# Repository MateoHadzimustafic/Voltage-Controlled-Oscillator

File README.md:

# Voltage-Controlled-Oscillator

## Overview

Designed and built a Voltage-Controlled Oscillator (VCO) capable of generating square and triangle waveforms with adjustable frequency and amplitude using op-amp-based analog circuitry. Integrated USB power management and LiPo battery input for portable or wired operation, including onboard LiPo charging functionality for convenient rechargeable power support.

## Current Status

Completed — Fully designed, built, tested, and validated.

## Features

- Square Wave Generator
- Triangle Wave Generator
- Frequency Control
- Amplitude Control
- Lipo Battery and USB-C Powered
- Lipo Battery Charger

## Repository Structure

- `docs/` — design notes, calculations, and planning
- `hardware/` — schematic, PCB layout, and manufacturing files
- `bom/` — bill of materials and component notes
- `images/` — renders, diagrams, and photos

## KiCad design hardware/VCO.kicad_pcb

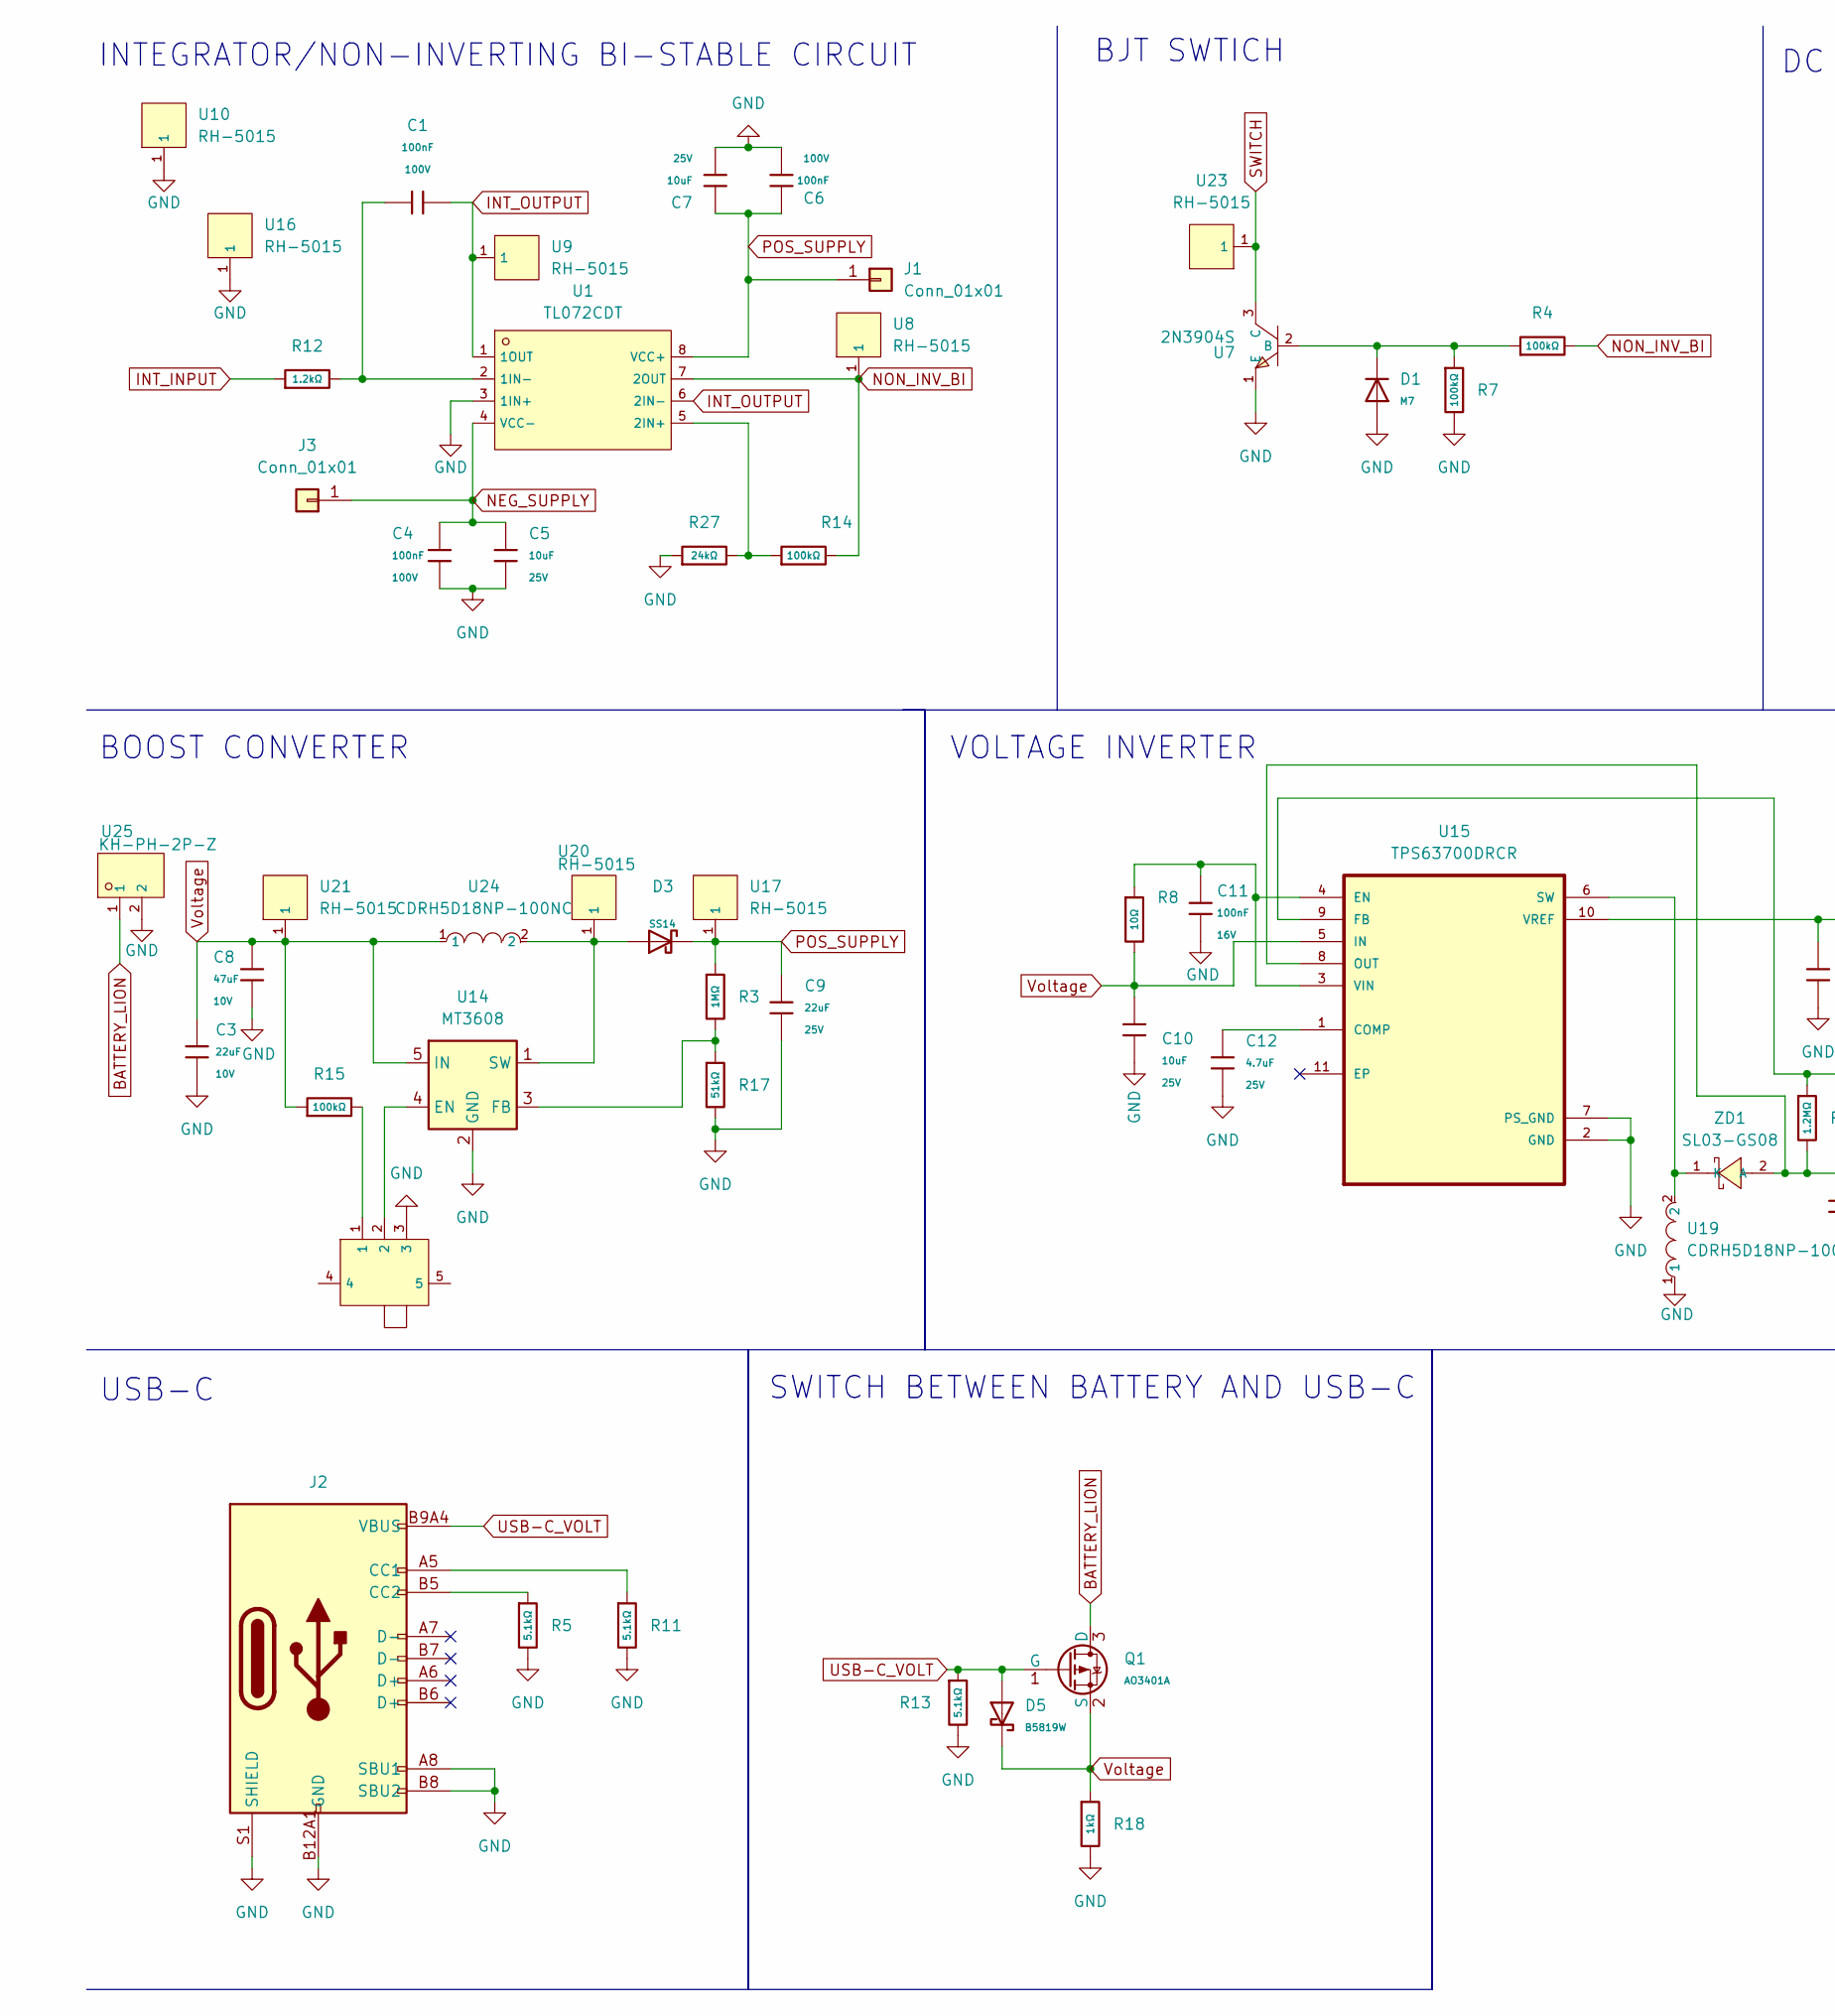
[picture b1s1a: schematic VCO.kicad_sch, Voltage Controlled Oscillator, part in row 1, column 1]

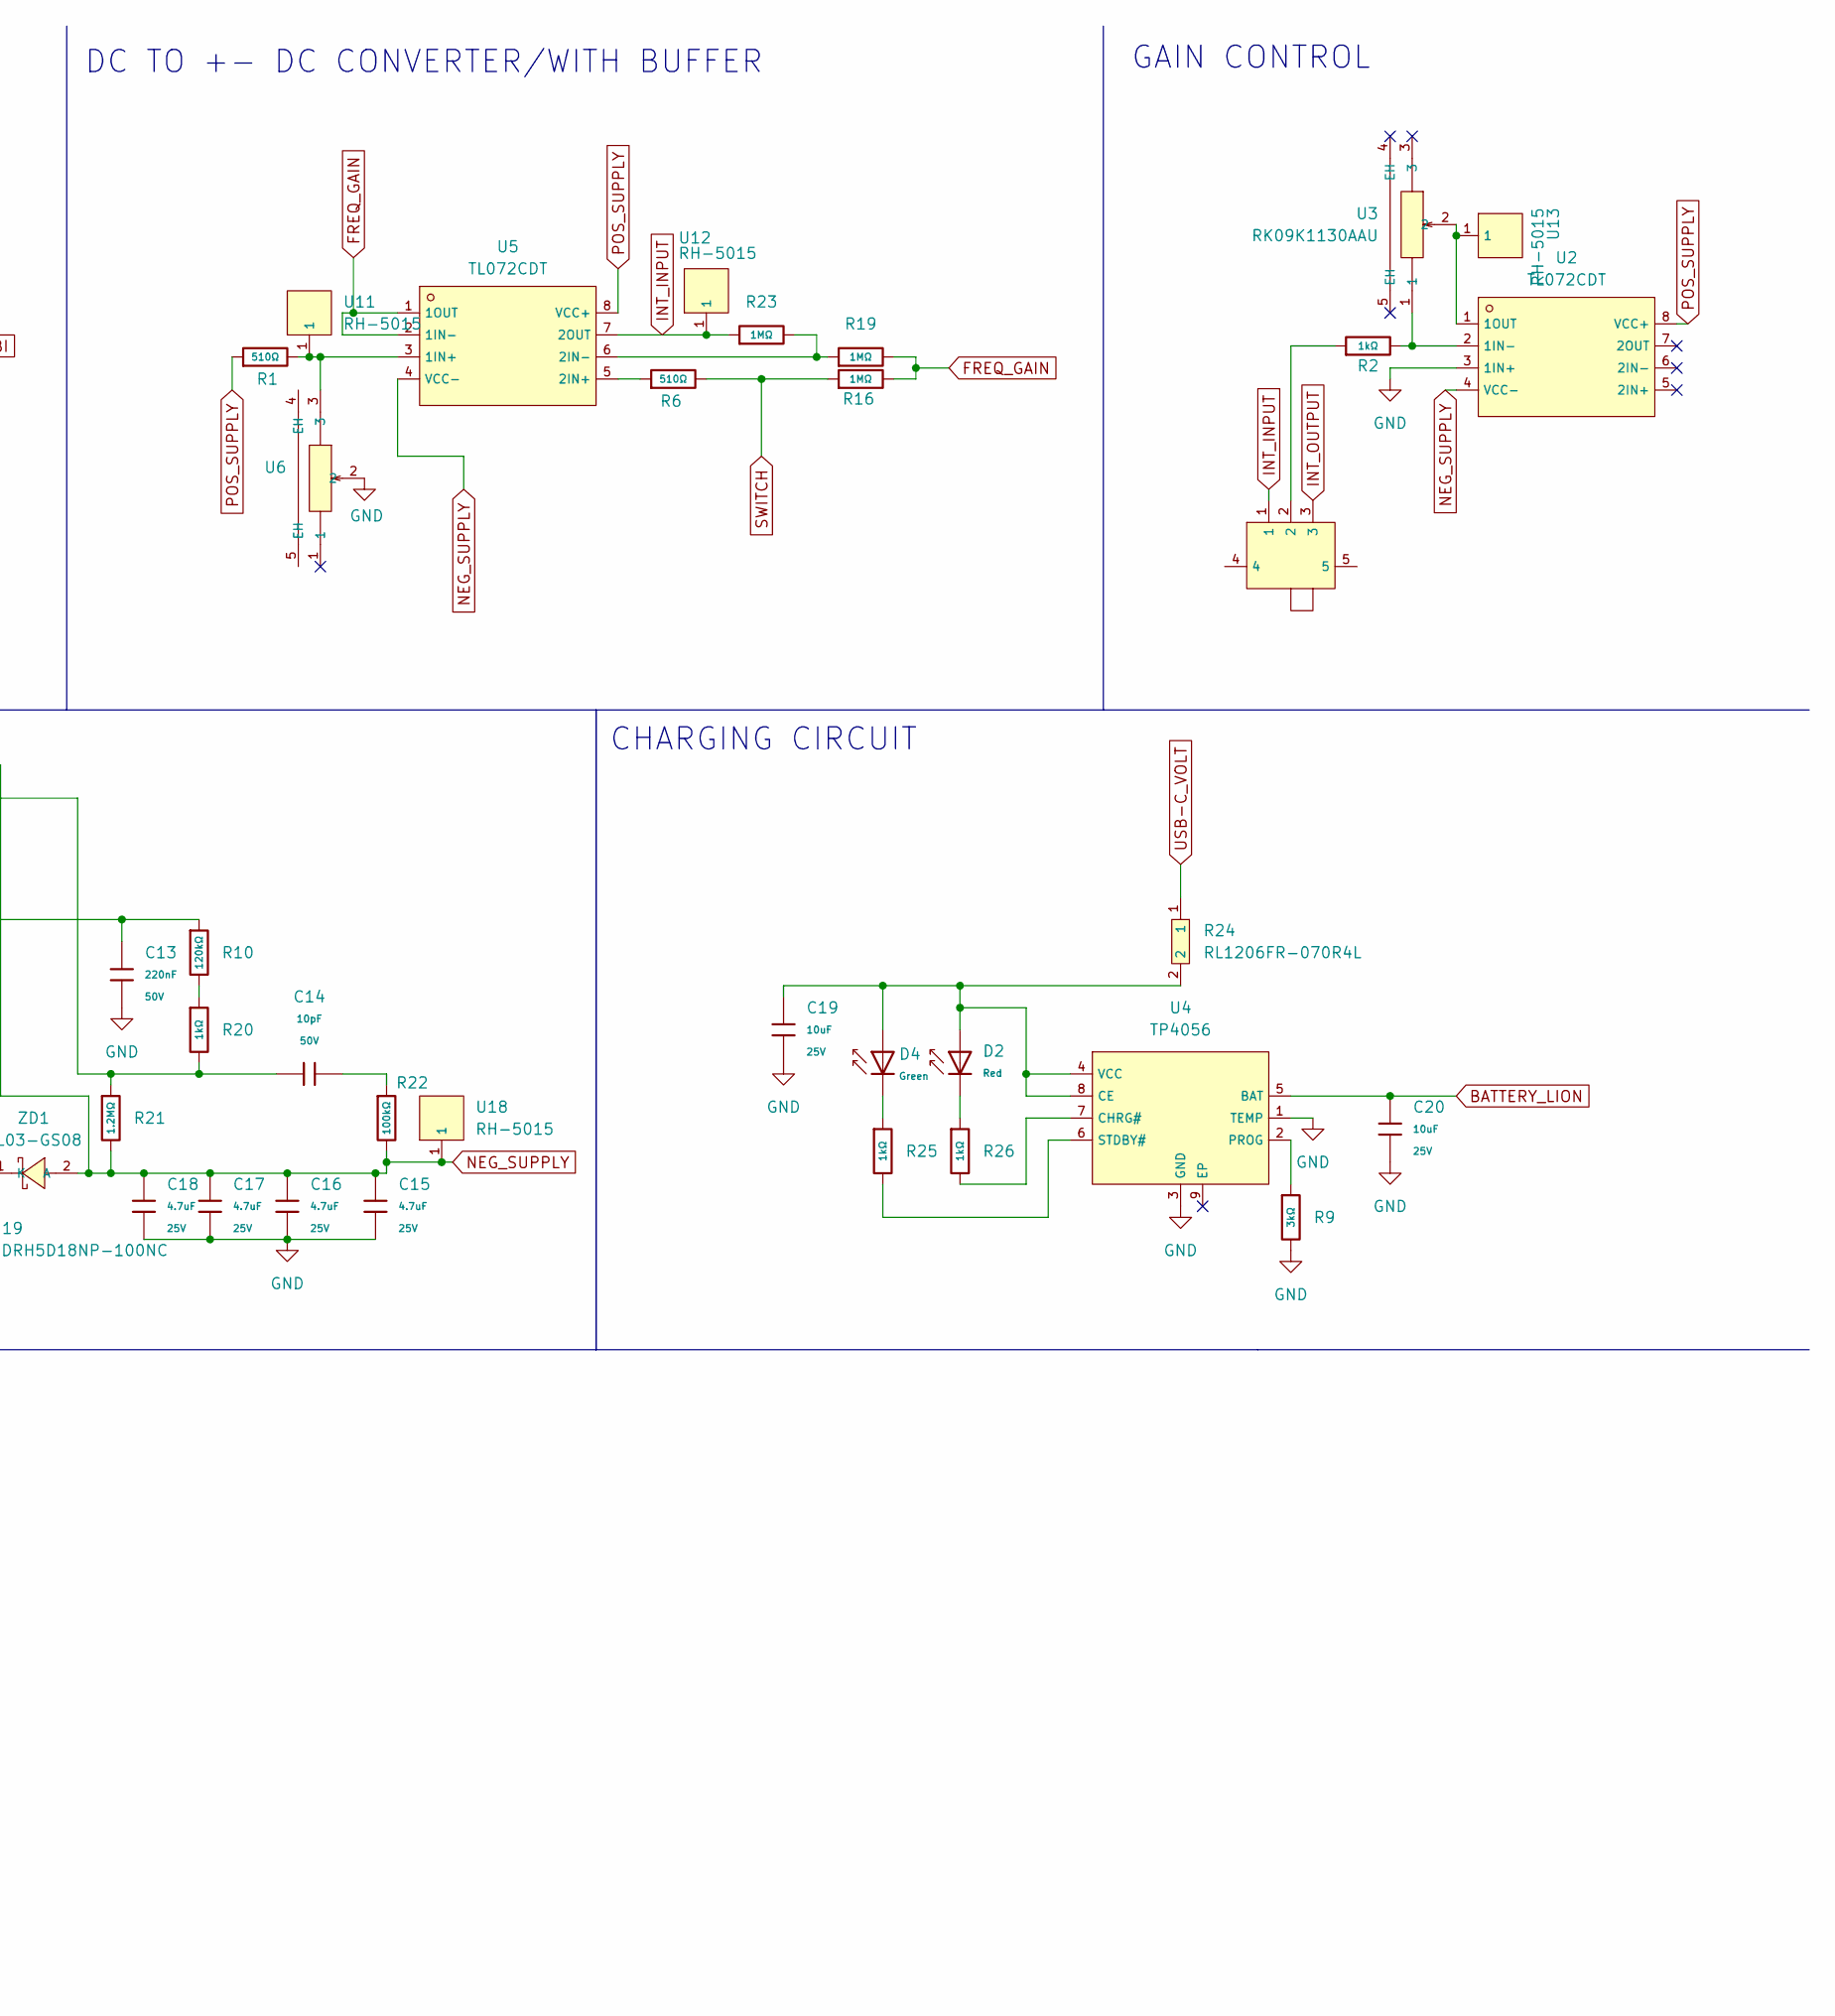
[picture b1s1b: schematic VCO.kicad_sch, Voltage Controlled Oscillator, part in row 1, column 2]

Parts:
C1, C4, C6: 100nF; C_0805; Voltage Rated 100V; Tolerance ±10%; Part CL21B104KCFNNNE; LCSC C28233
C3: 22uF; C_1206; Voltage Rated 10V; Tolerance ±10%; Part CL31A226KPHNNNE; LCSC C5672
C5, C7, C10, C19, C20: 10uF; C_0805; Voltage Rated 25V; Tolerance ±10%; Part CL21A106KAYNNNE; LCSC C15850
C8: 47uF; C_1206; Voltage Rated 10V; Tolerance ±20%; Part CL31A476MPHNNNE; LCSC C96123
C9: 22uF; C_0805; Voltage Rated 25V; Tolerance ±20%; Part CL21A226MAQNNNE; LCSC C45783
C11: 100nF; C_0402; Voltage Rated 16V; Tolerance ±10%; Part CL05B104KO5NNNC; LCSC C1525
C12, C15, C16, C17, C18: 4.7uF; C_0805; Voltage Rated 25V; Tolerance ±10%; Part CL21A475KAQNNNE; LCSC C1779
C13: 220nF; C_0805; Voltage Rated 50V; Tolerance ±10%; Part CL21B224KBFNNNE; LCSC C5378
C14: 10pF; C_0603; Voltage Rated 50V; Tolerance ±5%; Part CL10C100JB8NNNC; LCSC C1634
D1: M7; D_SMA; Forward Voltage (Vf@If) 1.1V@1A; Reverse Voltage (Vr) 1kV; Part M7; LCSC C95872
D2: Red; D_0805; Forward Voltage (VF) 1.6V~2.6V; Part NCD0805R1; LCSC C84256
D3: SS14; D_SMA; Forward Voltage (Vf@If) 0.55V@1.0A; Reverse Voltage (Vr) 40V; Part SS14; LCSC C7420316
D4: Green; D_0805; Part KT-0805G; LCSC C2297
D5: B5819W; D_SOD-123; Forward Voltage (Vf@If) 900mV@3A; Reverse Voltage (Vr) 40V; Part B5819W; LCSC C64885
J1, J3: Conn_01x01; PinHeader_1x01_P1.00mm_Vertical
J2: Connector, USB-TYPE-C-16P; TYPE-C-SMD_HX-TYPE-C-16PIN; LCSC C2927039
Q1: AO3401A; Q_SOT-23; Part AO3401A; LCSC C15127
R1, R6: 510Ω; R_0805; Overload Voltage (Max) 150V; Tolerance ±1%; Part 0805W8F5100T5E; LCSC C17734
R2, R18, R20, R25, R26: 1kΩ; R_0805; Overload Voltage (Max) 150V; Tolerance ±1%; Part 0805W8F1001T5E; LCSC C17513
R3, R16, R19, R23: 1MΩ; R_0805; Overload Voltage (Max) 150V; Tolerance ±1%; Part 0805W8F1004T5E; LCSC C17514
R4, R7, R14, R15, R22: 100kΩ; R_0805; Overload Voltage (Max) 150V; Tolerance ±1%; Part 0805W8F1003T5E; LCSC C149504
R5, R11, R13: 5.1kΩ; R_0805; Overload Voltage (Max) 150V; Tolerance ±1%; Part 0805W8F5101T5E; LCSC C27834
R8: 10Ω; R_0603; Overload Voltage (Max) 75V; Tolerance ±1%; Part 0603WAF100JT5E; LCSC C22859
R9: 3kΩ; R_0805; Overload Voltage (Max) 150V; Tolerance ±1%; Part 0805W8F3001T5E; LCSC C17661
R10: 120kΩ; R_0805; Overload Voltage (Max) 150V; Tolerance ±1%; Part 0805W8F1203T5E; LCSC C17436
R12: 1.2kΩ; R_0805; Overload Voltage (Max) 150V; Tolerance ±1%; Part 0805W8F1201T5E; LCSC C17379
R17: 51kΩ; R_0805; Overload Voltage (Max) 150V; Tolerance ±1%; Part 0805W8F5102T5E; LCSC C17737
R21: 1.2MΩ; R_1206; Overload Voltage (Max) 200V; Tolerance ±1%; Part 1206W4F1204T5E; LCSC C22107
R24: RL1206FR-070R4L; R1206; LCSC C327078
R27: 24kΩ; R_0805; Overload Voltage (Max) 150V; Tolerance ±1%; Part 0805W8F2402T5E; LCSC C17575
SW1, SW2: SS12D07VG6_087; SW-TH_SS12D07VG4; LCSC C2939728
U1, U2, U5: TL072CDT; SOIC-8_L5.0-W4.0-P1.27-LS6.0-BL; Voltage - Input Offset(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 3mV; Part TL072CDT; LCSC C6961
U3, U6: RK09K1130AAU; RES-TH_RK09K1130AAU; LCSC C202373
U4: TP4056; ESOP-8_L4.9-W3.9-P1.27-LS6.0-BL-EP; Part TP4056-42-ESOP8; LCSC C16581
U7: 2N3904S; SOT-23-3_L2.9-W1.3-P1.90-LS2.4-TR; LCSC C18536
U8, U9, U10, U11, U12, U13, U16, U17, U18, U20, U21, U23: RH-5015; SMD_RH-5015; LCSC C5199798
U14: MT3608; SOT-23-6_L2.9-W1.6-P0.95-LS2.8-BL; LCSC C84817
U15: TPS63700DRCR; VREG_V62_16624-01YE; LCSC C54792
U19, U24: CDRH5D18NP-100NC; IND-SMD_L5.7-W5.7_CDRH5D18NP; LCSC C113636
U25: KH-PH-2P-Z; CONN-TH_2P-P2.00_KINGHELM_KH-PH-2P-Z; LCSC C2898945
ZD1: SL03-GS08; SMF_L2.8-W1.8-LS3.7-RD; LCSC C490381

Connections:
BATTERY_LION: C20.1, Q1.3 (D), U4.5 (BAT), U25.1
FREQ_GAIN: R16.2, R19.2, U5.1 (1OUT), U5.2 (1IN-)
GND: C3.2, C4.2, C5.2, C6.2, C7.2, C8.2, C9.2, C10.2, C11.2, C12.2, C13.2, C15.2, C16.2, C17.2, C18.2, C19.2, C20.2, D1.2, J2.A8 (SBU1), J2.A12B1 (GND), J2.B8 (SBU2), J2.B12A1 (GND), J2.S1 (SHIELD), R5.2, R7.2, R9.2, R11.2, R13.2, R17.2, R18.2, R27.1, SW1.3, U1.3 (1IN+), U2.3 (1IN+), U4.1 (TEMP), U4.3 (GND), U6.2, U7.1 (E), U10.1, U14.2 (GND), U15.2 (GND), U15.7 (PS_GND), U16.1, U19.1, U25.2
INT_INPUT: R12.1, R23.1, SW2.1, U5.7 (2OUT), U12.1
INT_OUTPUT: C1.2, SW2.3, U1.1 (1OUT), U1.6 (2IN-), U9.1
NEG_SUPPLY: C4.1, C5.1, C15.1, C16.1, C17.1, C18.1, J3.1, R21.2, R22.2, U1.4 (VCC-), U2.4 (VCC-), U5.4 (VCC-), U15.8 (OUT), U18.1, ZD1.2 (A)
NON_INV_BI: R4.2, R14.2, U1.7 (2OUT), U8.1
unnamed: C14.2, R22.1
unnamed: D2.1, R26.1
unnamed: D4.1, R25.1
unnamed: J2.A5 (CC1), R11.1
unnamed: J2.B5 (CC2), R5.1
unnamed: R2.1, SW2.2
unnamed: R10.2, R20.1
unnamed: R15.2, SW1.1
unnamed: C1.1, R12.2, U1.2 (1IN-)
unnamed: R14.1, R27.2, U1.5 (2IN+)
unnamed: R2.2, U2.2 (1IN-), U3.1
unnamed: U2.1 (1OUT), U3.2, U13.1
unnamed: C19.1, D2.2, D4.2, R24.2, U4.4 (VCC), U4.8 (CE)
unnamed: R26.2, U4.7 (CHRG#)
unnamed: R9.1, U4.2 (PROG)
unnamed: R25.2, U4.6 (STDBY#)
unnamed: R1.2, U5.3 (1IN+), U6.3, U11.1
unnamed: R6.1, U5.5 (2IN+)
unnamed: R19.1, R23.2, U5.6 (2IN-)
unnamed: D1.1, R4.1, R7.1, U7.2 (B)
unnamed: SW1.2, U14.4 (EN)
unnamed: R3.2, R17.1, U14.3 (FB)
unnamed: D3.2, U14.1 (SW), U20.1, U24.2
unnamed: C12.1, U15.1 (COMP)
unnamed: C11.1, R8.1, U15.3 (VIN), U15.4 (EN)
unnamed: C14.1, R20.2, R21.1, U15.9 (FB)
unnamed: U15.6 (SW), U19.2, ZD1.1 (K)
unnamed: C13.1, R10.1, U15.10 (VREF)
POS_SUPPLY: C6.1, C7.1, C9.1, D3.1, J1.1, R1.1, R3.1, U1.8 (VCC+), U2.8 (VCC+), U5.8 (VCC+), U17.1
SWITCH: R6.2, R16.1, U7.3 (C), U23.1
USB-C_VOLT: D5.2, J2.A9B4 (VBUS), J2.B9A4 (VBUS), Q1.1 (G), R13.1, R24.1
Voltage: C3.1, C8.1, C10.1, D5.1, Q1.2 (S), R8.2, R15.1, R18.1, U14.5 (IN), U15.5 (IN), U21.1, U24.1

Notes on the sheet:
BJT SWTICH
GAIN CONTROL
VOLTAGE INVERTER
DC TO +- DC CONVERTER/WITH BUFFER
CHARGING CIRCUIT
SWITCH BETWEEN BATTERY AND USB-C
USB-C
INTEGRATOR/NON-INVERTING BI-STABLE CIRCUIT
BOOST CONVERTER

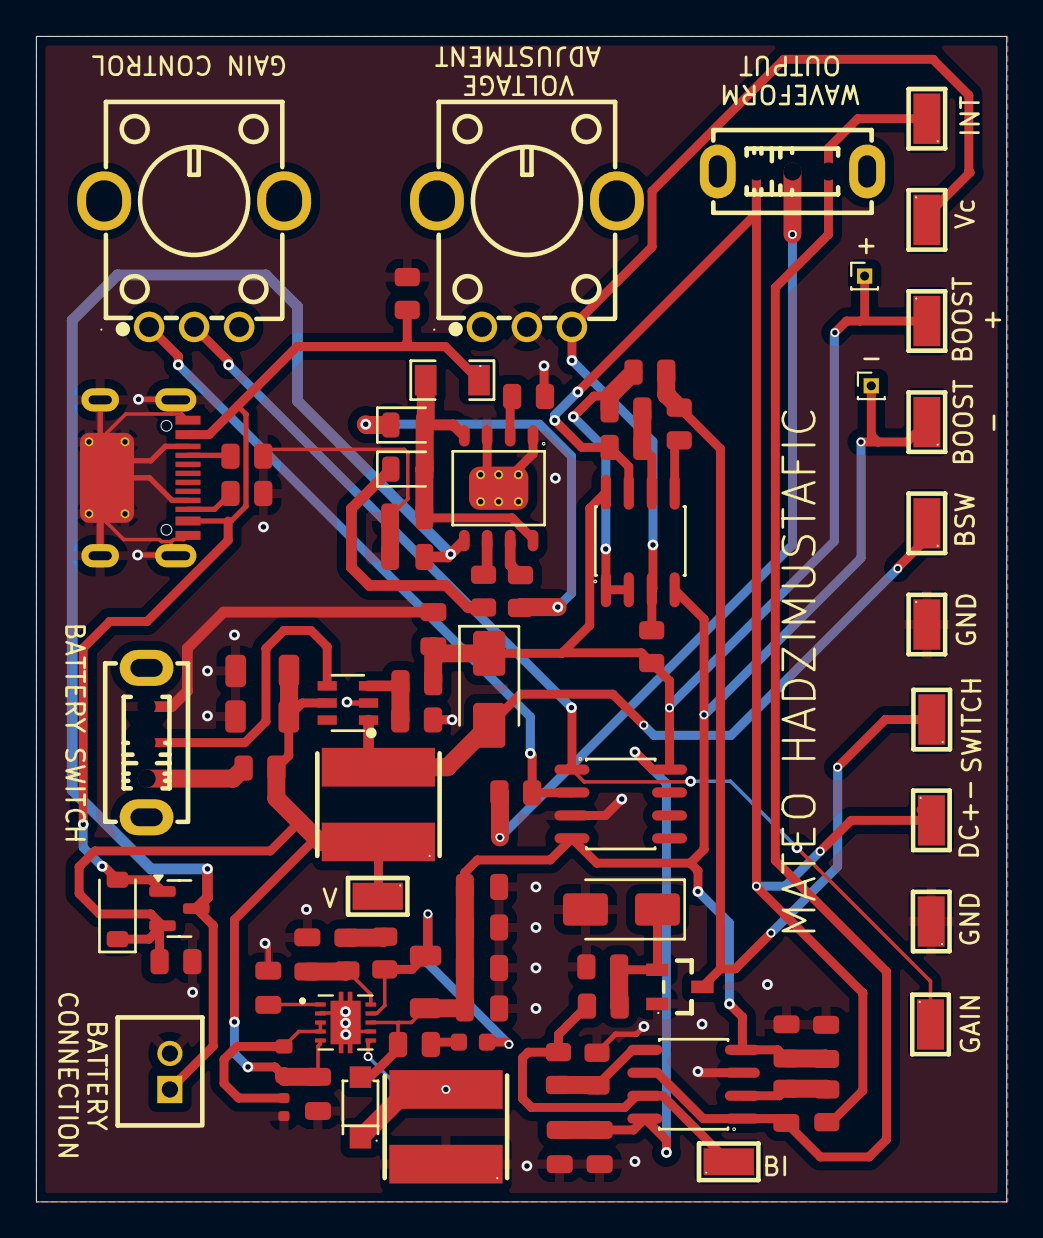
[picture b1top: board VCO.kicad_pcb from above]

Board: 2 copper layers, 53.9 x 64.8 mm, 82 parts (0 on the bottom side), 39 nets.

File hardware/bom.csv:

Designator,Footprint,Quantity,Value,LCSC Part #
"C1, C4, C6",C_0805,3,100nF,C28233
"C10, C19, C20, C5, C7",C_0805,5,10uF,C15850
C11,C_0402,1,100nF,C1525
"C12, C15, C16, C17, C18",C_0805,5,4.7uF,C1779
C13,C_0805,1,220nF,C5378
C14,C_0603,1,10pF,C1634
C3,C_1206,1,22uF,C5672
C8,C_1206,1,47uF,C96123
C9,C_0805,1,22uF,C45783
D1,D_SMA,1,M7,C95872
D2,D_0805,1,Red,C84256
D3,D_SMA,1,SS14,C7420316
D4,D_0805,1,Green,C2297
D5,D_SOD-123,1,B5819W,C64885
"J1, J3",PinHeader_1x01_P1.00mm_Vertical,2,Conn_01x01,
J2,TYPE-C-SMD_HX-TYPE-C-16PIN,1,"Connector, USB-TYPE-C-16P",C2927039
Q1,Q_SOT-23,1,AO3401A,C15127
"R1, R6",R_0805,2,510Ω,C17734
R10,R_0805,1,120kΩ,C17436
"R11, R13, R5",R_0805,3,5.1kΩ,C27834
R12,R_0805,1,1.2kΩ,C17379
"R14, R15, R22, R4, R7",R_0805,5,100kΩ,C149504
"R16, R19, R23, R3",R_0805,4,1MΩ,C17514
R17,R_0805,1,51kΩ,C17737
"R18, R2, R20, R25, R26",R_0805,5,1kΩ,C17513
R21,R_1206,1,1.2MΩ,C22107
R24,R1206,1,RL1206FR-070R4L,C327078
R27,R_0805,1,24kΩ,C17575
R8,R_0603,1,10Ω,C22859
R9,R_0805,1,3kΩ,C17661
"SW1, SW2",SW-TH_SS12D07VG4,2,SS12D07VG6_087,C2939728
"U1, U2, U5",SOIC-8_L5.0-W4.0-P1.27-LS6.0-BL,3,TL072CDT,C6961
"U10, U11, U12, U13, U16, U17, U18, U20, U21, U23, U8, U9",SMD_RH-5015,12,RH-5015,C5199798
U14,SOT-23-6_L2.9-W1.6-P0.95-LS2.8-BL,1,MT3608,C84817
U15,VREG_V62_16624-01YE,1,TPS63700DRCR,C54792
"U19, U24",IND-SMD_L5.7-W5.7_CDRH5D18NP,2,CDRH5D18NP-100NC,C113636
U25,CONN-TH_2P-P2.00_KINGHELM_KH-PH-2P-Z,1,KH-PH-2P-Z,C2898945
"U3, U6",RES-TH_RK09K1130AAU,2,RK09K1130AAU,C202373
U4,ESOP-8_L4.9-W3.9-P1.27-LS6.0-BL-EP,1,TP4056,C16581
U7,SOT-23-3_L2.9-W1.3-P1.90-LS2.4-TR,1,2N3904S,C18536
ZD1,SMF_L2.8-W1.8-LS3.7-RD,1,SL03-GS08,C490381

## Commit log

2026-04-28 Create schematic
2026-04-28 Create testing
2026-04-28 Create bom
